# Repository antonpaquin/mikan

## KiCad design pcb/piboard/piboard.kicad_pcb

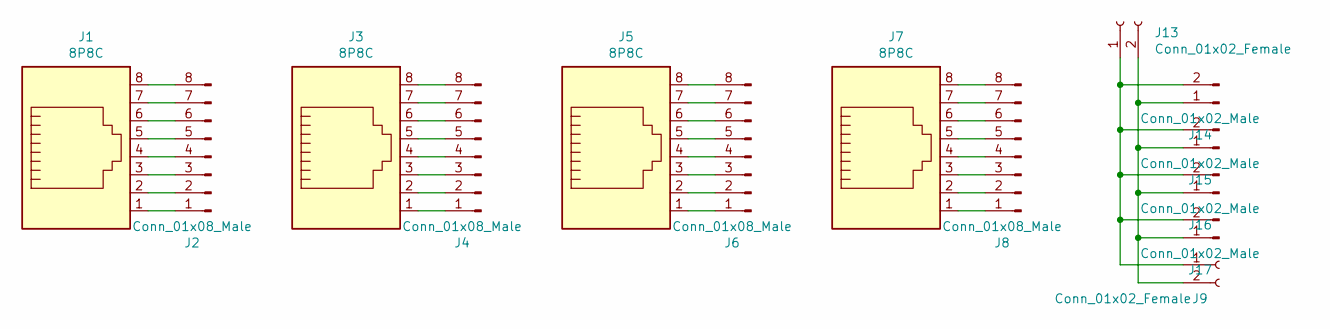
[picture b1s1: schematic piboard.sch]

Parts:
J1, J3, J5, J7: 8P8C; Assmann A-2014-2S-4-N-R
J2, J4, J6, J8: Conn_01x08_Male; rj45-throughhole-staggered
J9, J13: Conn_01x02_Female; Molex_Sabre_43160-XX02_02x7.49mm_Vertical_BoardLock
J14, J15, J16, J17: Conn_01x02_Male; barrel-1.8mm

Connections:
unnamed: J1.1, J2.1
unnamed: J1.2, J2.2
unnamed: J1.3, J2.3
unnamed: J1.4, J2.4
unnamed: J1.5, J2.5
unnamed: J1.6, J2.6
unnamed: J1.7, J2.7
unnamed: J1.8, J2.8
unnamed: J3.1, J4.1
unnamed: J3.2, J4.2
unnamed: J3.3, J4.3
unnamed: J3.4, J4.4
unnamed: J3.5, J4.5
unnamed: J3.6, J4.6
unnamed: J3.7, J4.7
unnamed: J3.8, J4.8
unnamed: J5.1, J6.1
unnamed: J5.2, J6.2
unnamed: J5.3, J6.3
unnamed: J5.4, J6.4
unnamed: J5.5, J6.5
unnamed: J5.6, J6.6
unnamed: J5.7, J6.7
unnamed: J5.8, J6.8
unnamed: J7.1, J8.1
unnamed: J7.2, J8.2
unnamed: J7.3, J8.3
unnamed: J7.4, J8.4
unnamed: J7.5, J8.5
unnamed: J7.6, J8.6
unnamed: J7.7, J8.7
unnamed: J7.8, J8.8
unnamed: J9.1, J13.1, J14.2, J15.2, J16.2, J17.2
unnamed: J9.2, J13.2, J14.1, J15.1, J16.1, J17.1

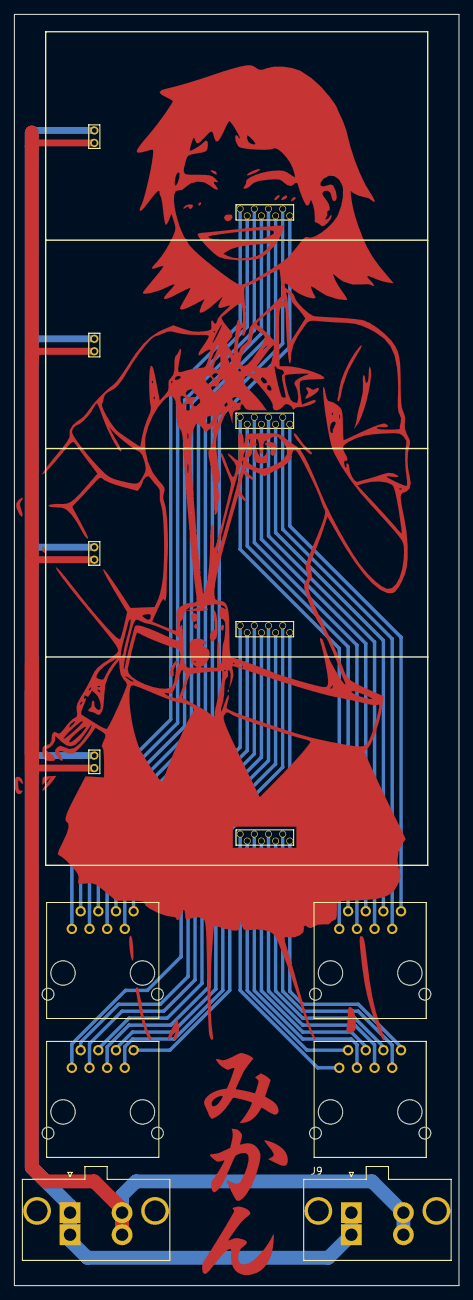
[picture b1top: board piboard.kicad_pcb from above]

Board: 2 copper layers, 64.0 x 183.0 mm, 14 parts (0 on the bottom side), 34 nets.

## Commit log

2019-05-25 Backup spark -- not enough ram, going to go with dask instead
2019-06-24 mikan-cluster
2019-06-24 Move to scope salt within project
2019-06-24 Add PCB
